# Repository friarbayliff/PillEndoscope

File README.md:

# Tiny Wireless Capsule Camera
OSH Pill Endoscopy

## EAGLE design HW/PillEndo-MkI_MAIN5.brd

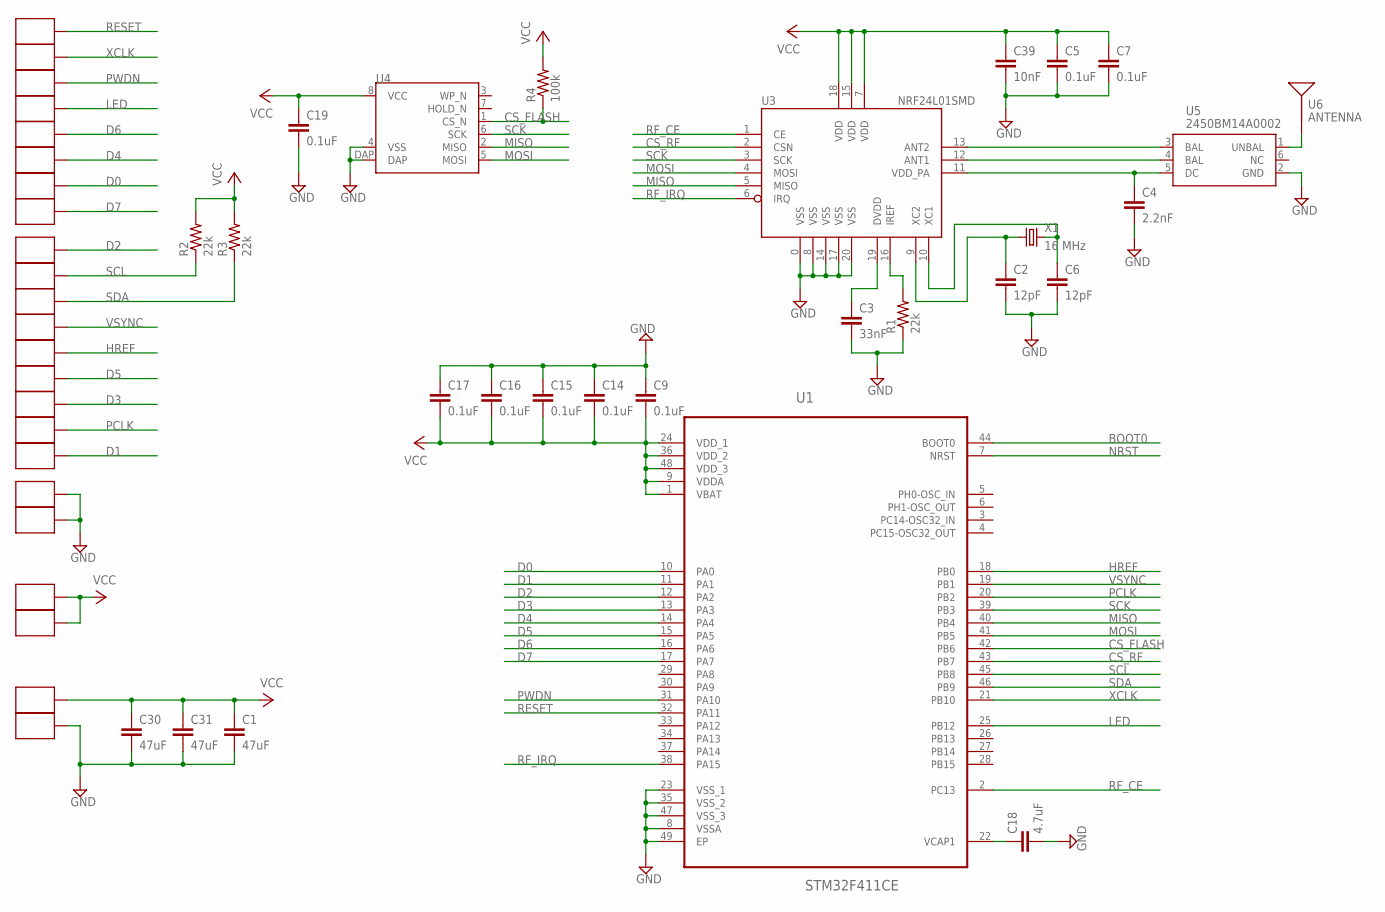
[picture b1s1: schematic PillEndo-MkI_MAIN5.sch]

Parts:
C1, C30, C31: 47uF; C0603
C2, C6: 12pF; C0402
C3: 33nF; C0402
C4: 2.2nF; C0402
C5, C7, C9, C14, C15, C16, C17, C19: 0.1uF; C0402
C18: 4.7uF; C0402
C39: 10nF; C0402
R1, R2, R3: 22k; R0402
R4: 100k; R0402
TP1, TP2, TP3, TP4, TP5, TP6, TP7, TP8, TP9, TP11, TP13, TP14, TP15, TP16, TP33, TP34, TP35: TP_0.8X1.2
TP10, TP12, TP17, TP18, TP19, TP20: TP_TP1.0X2.2; TP_1.0X2.2
U1: STM32F411CE; QFN50P700X700X60-49N
U3: NRF24L01SMD; QFN20
U4: S25FL256S; WSON_6X8
U5: 2450BM14A0002; 2450BM14A0002T
U6: ANTENNA; 2450AT18A100
X1: 16 MHz; CRYSTAL_FA20H

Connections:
BOOT0: U1.44 (BOOT0)
CS_FLASH: R4.1, U1.42 (PB6), U4.1 (CS_N)
CS_RF: U1.43 (PB7), U3.2 (CSN)
D0: TP7.P$1, U1.10 (PA0)
D1: TP34.P$1, U1.11 (PA1)
D2: TP9.P$1, U1.12 (PA2)
D3: TP16.P$1, U1.13 (PA3)
D4: TP6.P$1, U1.14 (PA4)
D5: TP15.P$1, U1.15 (PA5)
D6: TP5.P$1, U1.16 (PA6)
D7: TP8.P$1, U1.17 (PA7)
GND: C1.2, C2.2, C3.2, C4.2, C5.2, C6.2, C7.2, C9.1, C14.1, C15.1, C16.1, C17.1, C18.2, C19.2, C30.2, C31.2, C39.2, R1.1, TP10.P$1, TP12.P$1, TP17.P$1, U1.8 (VSSA), U1.23 (VSS_1), U1.35 (VSS_2), U1.47 (VSS_3), U1.49 (EP), U3.0 (VSS), U3.8 (VSS), U3.14 (VSS), U3.17 (VSS), U3.20 (VSS), U4.4 (VSS), U4.DAP, U5.2 (GND)
HREF: TP14.P$1, U1.18 (PB0)
LED: TP4.P$1, U1.25 (PB12)
MISO: U1.40 (PB4), U3.5 (MISO), U4.2 (MISO)
MOSI: U1.41 (PB5), U3.4 (MOSI), U4.5 (MOSI)
unnamed: C3.1, U3.19 (DVDD)
unnamed: C2.1, U3.9 (XC2), X1.1
unnamed: C6.1, U3.10 (XC1), X1.3 (2)
unnamed: R1.2, U3.16 (IREF)
unnamed: C4.1, U3.11 (VDD_PA), U5.5 (DC)
unnamed: U3.12 (ANT1), U5.4 (BAL)
unnamed: U3.13 (ANT2), U5.3 (BAL)
unnamed: U5.1 (UNBAL), U6.1
unnamed: C18.1, U1.22 (VCAP1)
NRST: U1.7 (NRST)
PCLK: TP33.P$1, U1.20 (PB2)
PWDN: TP3.P$1, U1.31 (PA10)
RESET: TP1.P$1, U1.32 (PA11)
RF_CE: U1.2 (PC13), U3.1 (CE)
RF_IRQ: U1.38 (PA15), U3.6 (IRQ)
SCK: U1.39 (PB3), U3.3 (SCK), U4.6 (SCK)
SCL: R2.1, TP11.P$1, U1.45 (PB8)
SDA: R3.1, TP35.P$1, U1.46 (PB9)
VCC: C1.1, C5.1, C7.1, C9.2, C14.2, C15.2, C16.2, C17.2, C19.1, C30.1, C31.1, C39.1, R2.2, R3.2, R4.2, TP18.P$1, TP19.P$1, TP20.P$1, U1.1 (VBAT), U1.9 (VDDA), U1.24 (VDD_1), U1.36 (VDD_2), U1.48 (VDD_3), U3.7 (VDD), U3.15 (VDD), U3.18 (VDD), U4.8 (VCC)
VSYNC: TP13.P$1, U1.19 (PB1)
XCLK: TP2.P$1, U1.21 (PB10)

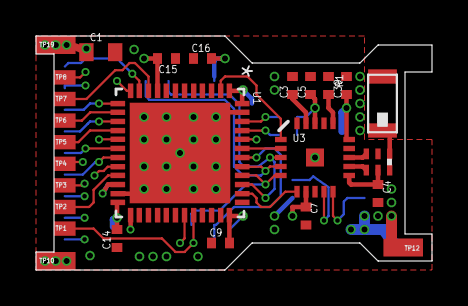
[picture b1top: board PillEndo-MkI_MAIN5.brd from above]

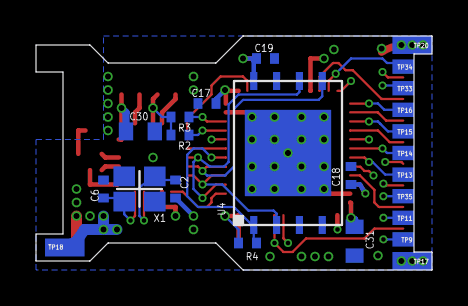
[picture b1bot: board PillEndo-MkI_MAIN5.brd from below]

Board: 4 copper layers, 22.0 x 13.0 mm, 50 parts (24 on the bottom side), 35 nets.

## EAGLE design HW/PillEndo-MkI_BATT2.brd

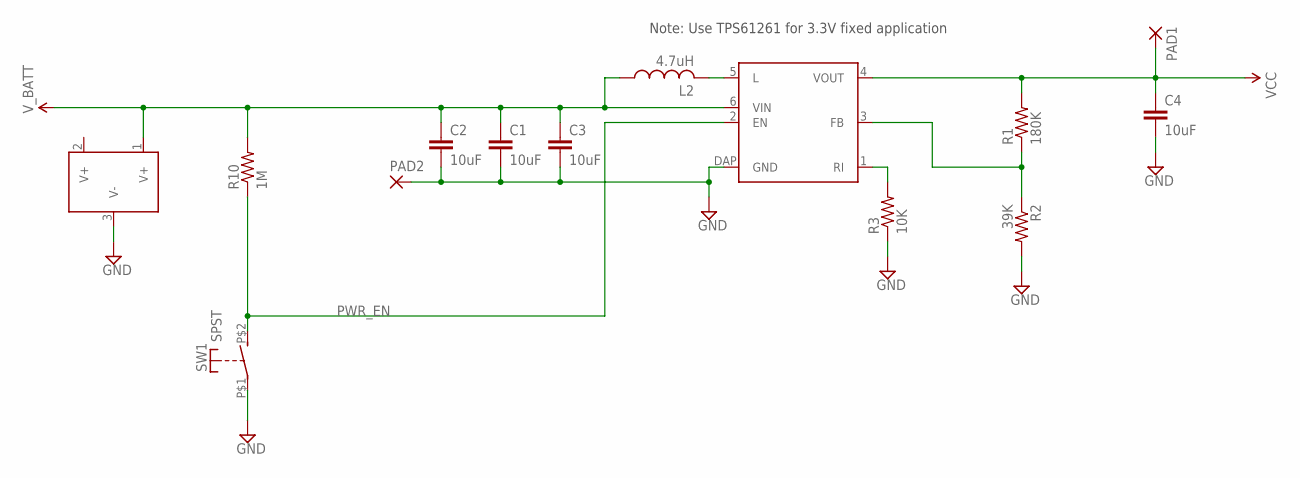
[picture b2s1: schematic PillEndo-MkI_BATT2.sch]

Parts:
C1, C2, C3, C4: 10uF; C0603
J1: BATT_7.9MM_TH; BATT_CLIP_7.9MM_TH
L2: 4.7uH; L0603
PAD1, PAD2: SMD2; SMD1,27-2,54
R1: 180K; R0402
R2: 39K; R0402
R3: 10K; R0402
R10: 1M; R0402
SW1: SPST; CT05
U2: TPS61260; S-PWSON-N6

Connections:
GND: C1.2, C2.2, C3.2, C4.2, J1.3 (V-), PAD2.1, R2.2, R3.1, SW1.P$1, U2.DAP (GND)
unnamed: L2.2, U2.5 (L)
unnamed: R1.1, R2.1, U2.3 (FB)
unnamed: R3.2, U2.1 (RI)
PWR_EN: R10.1, SW1.P$2 (S), U2.2 (EN)
VCC: C4.1, PAD1.1, R1.2, U2.4 (VOUT)
V_BATT: C1.1, C2.1, C3.1, J1.1 (V+), L2.1, R10.2, U2.6 (VIN)

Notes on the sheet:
Note: Use TPS61261 for 3.3V fixed application

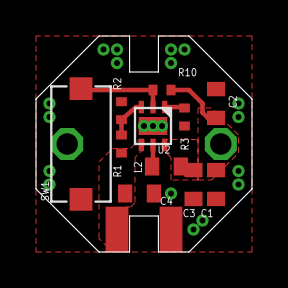
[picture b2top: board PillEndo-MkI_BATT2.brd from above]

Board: 2 copper layers, 12.0 x 12.0 mm, 14 parts (1 on the bottom side), 7 nets.

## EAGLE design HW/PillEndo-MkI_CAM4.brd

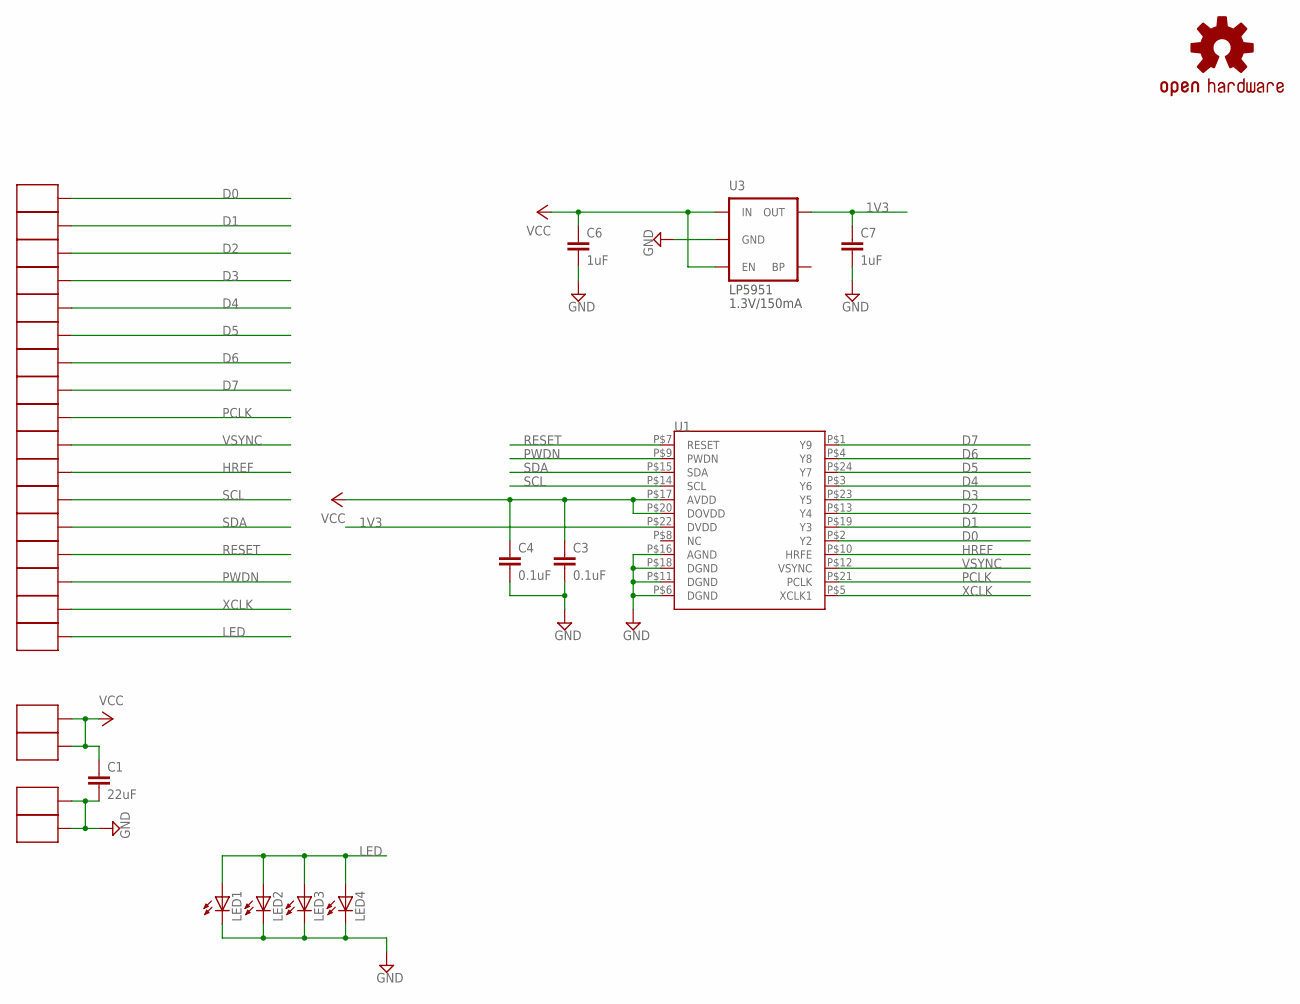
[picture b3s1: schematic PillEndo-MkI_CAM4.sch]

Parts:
C1: 22uF; C0603
C3, C4: 0.1uF; C0201
C6, C7: 1uF; C0402
LED1, LED2, LED3, LED4: LED; SMARTLED-TTW
LOGO1: OSHW-LOGOS; OSHW-LOGO-S
TP1, TP2, TP3, TP4, TP5, TP6, TP7, TP8, TP9, TP10, TP11, TP12, TP13, TP14, TP15, TP16, TP17: TP_0.8X0.8
TP18, TP19, TP20, TP21: TP_1.0X1.2
U1: UC2640B
U3: 1.8V/100mA; SC70

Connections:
1V3: C7.1, U1.P$22 (DVDD), U3.5 (OUT)
D0: TP11.P$1, U1.P$2 (Y2)
D1: TP1.P$1, U1.P$19 (Y3)
D2: TP9.P$1, U1.P$13 (Y4)
D3: TP3.P$1, U1.P$23 (Y5)
D4: TP12.P$1, U1.P$3 (Y6)
D5: TP4.P$1, U1.P$24 (Y7)
D6: TP13.P$1, U1.P$4 (Y8)
D7: TP10.P$1, U1.P$1 (Y9)
GND: C1.2, C3.2, C4.2, C6.2, C7.2, LED1.C@1 (C), LED2.C@1 (C), LED3.C@1 (C), LED4.C@1 (C), TP18.P$1, TP19.P$1, U1.P$6 (DGND), U1.P$11 (DGND), U1.P$16 (AGND), U1.P$18 (DGND), U3.2 (GND)
HREF: TP5.P$1, U1.P$10 (HRFE)
LED: LED1.A@1 (A), LED2.A@1 (A), LED3.A@1 (A), LED4.A@1 (A), TP14.P$1
PCLK: TP2.P$1, U1.P$21 (PCLK)
PWDN: TP15.P$1, U1.P$9 (PWDN)
RESET: TP17.P$1, U1.P$7 (RESET)
SCL: TP8.P$1, U1.P$14 (SCL)
SDA: TP7.P$1, U1.P$15 (SDA)
VCC: C1.1, C3.1, C4.1, C6.1, TP20.P$1, TP21.P$1, U1.P$17 (AVDD), U1.P$20 (DOVDD), U3.1 (IN), U3.3 (EN)
VSYNC: TP6.P$1, U1.P$12 (VSYNC)
XCLK: TP16.P$1, U1.P$5 (XCLK1)

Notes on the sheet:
LP5951
1.3V/150mA

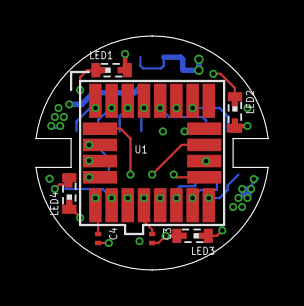
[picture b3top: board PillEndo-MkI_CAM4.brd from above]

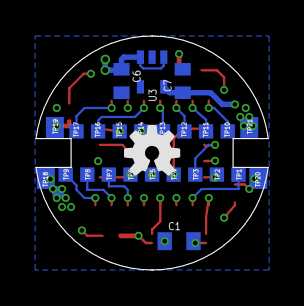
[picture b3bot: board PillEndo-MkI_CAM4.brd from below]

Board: 4 copper layers, 12.9 x 13.0 mm, 33 parts (26 on the bottom side), 20 nets.

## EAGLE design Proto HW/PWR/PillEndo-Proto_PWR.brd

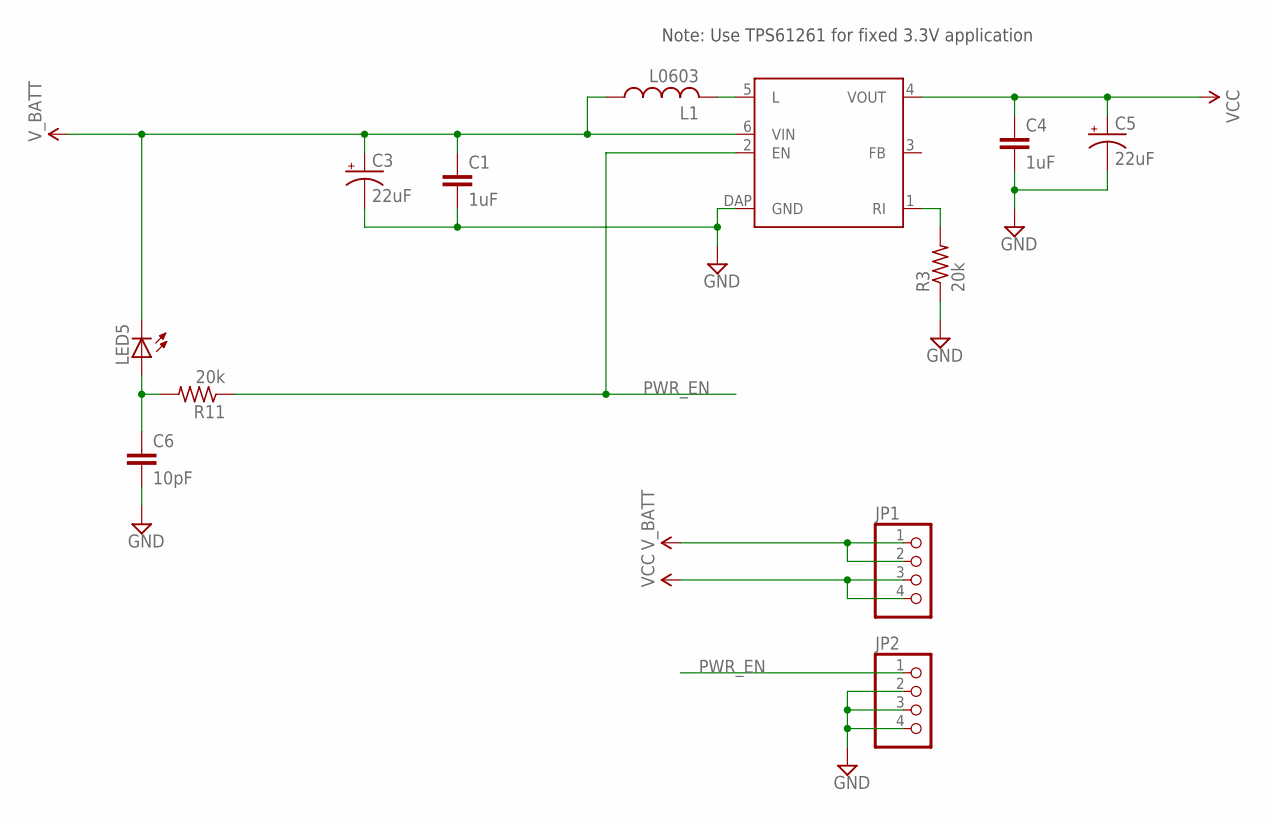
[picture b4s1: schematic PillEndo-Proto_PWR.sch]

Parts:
C1, C4: 1uF; C0603
C3, C5: 22uF; CT3216
C6: 10pF; C0603
JP1, JP2: PINHD-1X4; 1X04
L1: L0603
LED5: LEDCHIP-LED0603; CHIP-LED0603
R3, R11: 20k; R0603
U1: TPS61260; S-PWSON-N6

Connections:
GND: C1.2, C3.-, C4.2, C5.-, JP2.2, JP2.3, JP2.4, R3.1, U1.DAP (GND)
unnamed: L1.2, U1.5 (L)
unnamed: R3.2, U1.1 (RI)
unnamed: C6.1, LED5.A, R11.2
PWR_EN: JP2.1, R11.1, U1.2 (EN)
VCC: C4.1, C5.+, JP1.3, JP1.4, U1.4 (VOUT)
V_BATT: C1.1, C3.+, JP1.1, JP1.2, L1.1, LED5.C, U1.6 (VIN)

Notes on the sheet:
Note: Use TPS61261 for fixed 3.3V application

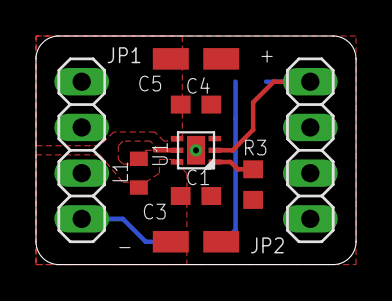
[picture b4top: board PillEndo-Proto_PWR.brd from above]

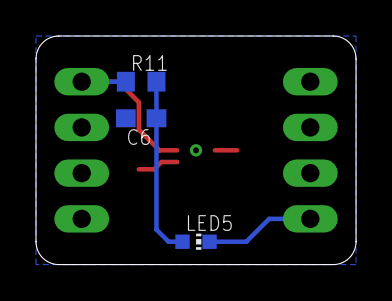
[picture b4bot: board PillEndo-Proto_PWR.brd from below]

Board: 2 copper layers, 17.8 x 12.7 mm, 12 parts (3 on the bottom side), 7 nets.

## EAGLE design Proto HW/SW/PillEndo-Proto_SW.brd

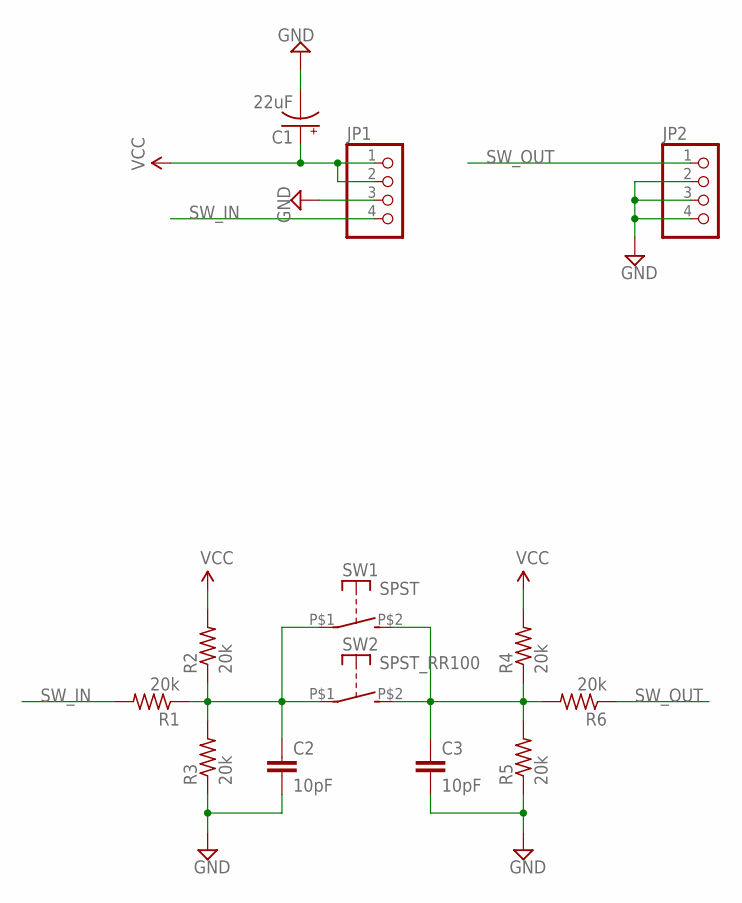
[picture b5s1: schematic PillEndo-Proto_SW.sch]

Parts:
C1: 22uF; CT3216
C2, C3: 10pF; C0603
JP1, JP2: PINHD-1X4; 1X04
R1, R2, R3, R4, R5, R6: 20k; R0603
SW1: SPST; CT05
SW2: SPST_RR100; RR100

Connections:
GND: C1.-, C2.2, C3.2, JP1.3, JP2.2, JP2.3, JP2.4, R3.1, R5.1
unnamed: C3.1, R4.1, R5.2, R6.2, SW1.P$2 (S), SW2.P$2 (S)
unnamed: C2.1, R1.1, R2.1, R3.2, SW1.P$1, SW2.P$1
SW_IN: JP1.4, R1.2
SW_OUT: JP2.1, R6.1
VCC: C1.+, JP1.1, JP1.2, R2.2, R4.2

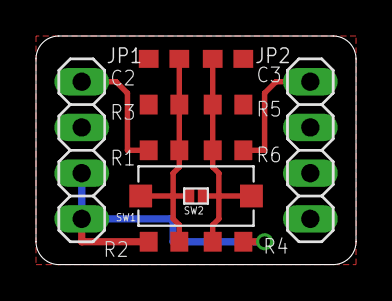
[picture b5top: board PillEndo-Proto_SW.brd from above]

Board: 2 copper layers, 17.8 x 12.7 mm, 13 parts (1 on the bottom side), 6 nets.

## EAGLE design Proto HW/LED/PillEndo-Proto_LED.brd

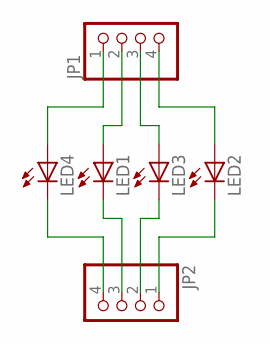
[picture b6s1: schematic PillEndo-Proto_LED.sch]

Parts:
JP1, JP2: PINHD-1X4; 1X04
LED1, LED2, LED3, LED4: LED; SMARTLED-TTW

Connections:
unnamed: JP2.2, LED3.C@1 (C)
unnamed: JP2.3, LED1.C@1 (C)
unnamed: JP2.1, LED2.C@1 (C)
unnamed: JP2.4, LED4.C@1 (C)
unnamed: JP1.3, LED3.A@1 (A)
unnamed: JP1.2, LED1.A@1 (A)
unnamed: JP1.1, LED4.A@1 (A)
unnamed: JP1.4, LED2.A@1 (A)

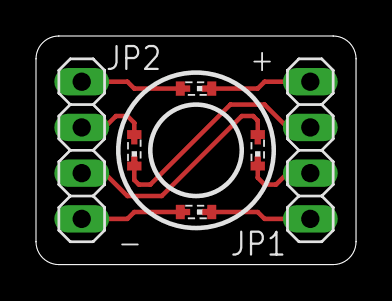
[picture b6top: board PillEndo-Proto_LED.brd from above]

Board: 2 copper layers, 17.8 x 12.7 mm, 6 parts (0 on the bottom side), 8 nets.

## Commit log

2015-07-22 Proto boards
    Initial prototyping boards
2016-04-25 Added files via upload

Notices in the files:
parts and their libraries:
SparkFun-Aesthetics: Licensing: Creative Commons ShareAlike 4.0 International - https://creativecommons.org/licenses/by-sa/4.0
